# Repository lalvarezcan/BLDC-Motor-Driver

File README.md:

# BLDC Motor Driver for MIT Mini Cheetah Actuator

This driver is designed specifically for use with the Quasi-Direct Driver (QDD) Actuators, inspired by the work of Ben Katz. The driver is intended to efficiently deliver power and control a BLDC Motor, enabling precise and agile movements.

## Overview

The BLDC Motor Driver is a crucial component in the Quasi-Driect Drive (QDD) Actuator system, responsible for managing the power and control signals sent to the brushless DC motors. It ensures smooth operation, speed control, and torque management for the actuators, contributing to the overall performance of the robotic system.

## Features

- **Brushless DC Motor Control:** Offers precise control over the motors used in the Mini Cheetah Actuator.
- **PWM (Pulse Width Modulation) Control:** Enables accurate speed control and torque management.
- **Communication Interface:** Interfaces with the main control system via a specified communication protocol (e.g., SPI, CAN, UART).
- **Overcurrent and Overvoltage Protection:** Safeguards the system and motors against potential damage due to excessive current or voltage.

## Hardware Requirements

- **BLDC Motors:** Compatible with the motors specified for the MIT Mini Cheetah Actuator.
- **Microcontroller or Control Board:** Interfaces with the driver to send control signals.
- **Power Supply:** Provides the necessary voltage and current for the motors.

## Installation and Setup

1. **Hardware Connections:** Connect the driver to the specified ports on the control board and motors as per the provided documentation or pinout details.
2. **Power Supply:** Ensure the power supply meets the voltage and current requirements of the motors.
3. **Control Interface:** Establish communication between the driver and the main control system using the designated communication protocol.
4. **Software Integration:** Implement the necessary control algorithms or software libraries to interact with the driver and control the motors effectively.

## Usage

- **Initialization:** Initialize the driver and configure the necessary parameters (e.g., PWM frequency, motor direction, etc.).
- **Control Commands:** Send control commands via the designated communication interface to adjust motor speed, direction, and torque as required.
- **Monitoring:** Implement monitoring mechanisms to keep track of motor performance, temperature, and any potential faults.

## Contributors

- Luis Avarez (CINVESTAV Guadalajara)

## License

This project is licensed under [MIT License](LICENSE.md).

## Acknowledgments

- Ben Katz (Original MIT Mini Cheetah Actuator Design)

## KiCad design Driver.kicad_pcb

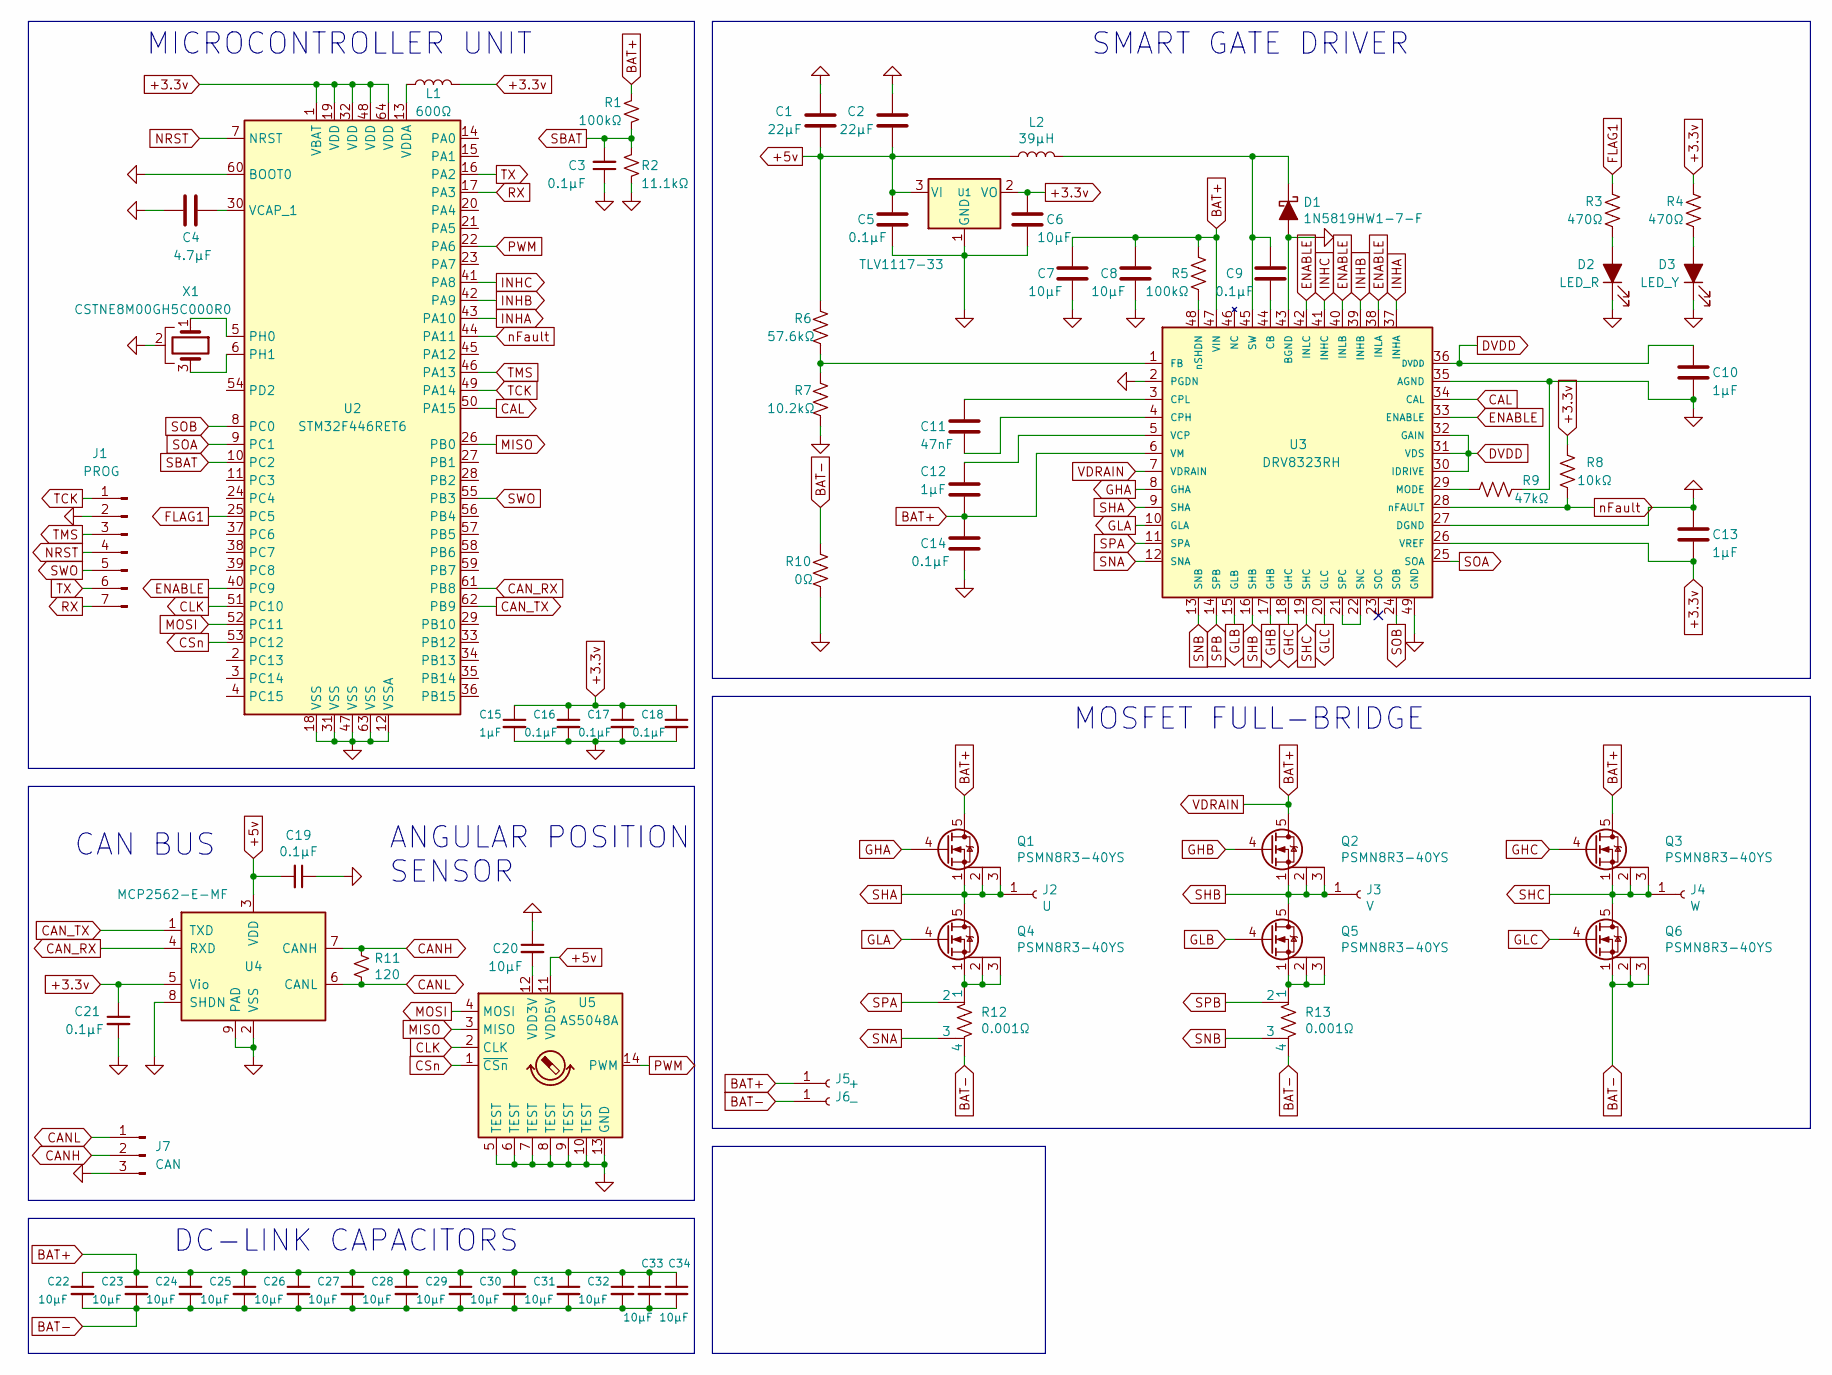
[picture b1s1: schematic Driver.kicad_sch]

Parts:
C1, C2: 22µF; C_0805_2012Metric
C3, C5, C9, C14, C16, C17, C18, C19, C21: 0.1µF; C_0805_2012Metric
C4: 4.7µF; C_0805_2012Metric
C6, C7, C8, C20: 10µF; C_0805_2012Metric
C10, C12, C13, C15: 1µF; C_0805_2012Metric
C11: 47nF; C_0805_2012Metric
C22, C23, C24, C25, C26, C27, C28, C29, C30, C31, C32, C33, C34: 10µF; C_1206_3216Metric
D1: 1N5819HW1-7-F; D_SOD-123F
D2: LED_R; LED_0603_1608Metric_Pad1.05x0.95mm_HandSolder
D3: LED_Y; LED_0603_1608Metric_Pad1.05x0.95mm_HandSolder
J1: PROG; JST_SH_SM07B-SRSS-TB_1x07-1MP_P1.00mm_Horizontal
J2: U; drillhole
J3: V; drillhole
J4: W; drillhole
J5: +; drillhole
J6: -; drillhole
J7: CAN; JST_SH_SM03B-SRSS-TB_1x03-1MP_P1.00mm_Horizontal
L1: 600Ω; L_0805_2012Metric
L2: 39µH; ELL6UH390M
Q1, Q2, Q3, Q4, Q5, Q6: PSMN8R3-40YS; LFPAK56
R1, R5: 100kΩ; R_0805_2012Metric
R2: 11.1kΩ; R_0805_2012Metric
R3, R4: 470Ω; R_0805_2012Metric
R6: 57.6kΩ; R_0805_2012Metric
R7: 10.2kΩ; R_0805_2012Metric
R8: 10kΩ; R_0805_2012Metric
R9: 47kΩ; R_0805_2012Metric
R10: 0Ω; R_1206_3216Metric
R11: 120; R_0805_2012Metric
R12, R13: 0.001Ω; R_Shunt_2512_6332Metric
U1: TLV1117-33; Texas_S-PVSON-N8
U2: STM32F446RET6; LQFP-64_10x10mm_P0.5mm
U3: DRV8323RH; Texas_S-PVQFN-N48_EP5.15x5.15mm_ThermalVias
U4: MCP2562-E-MF; DFN-8-1EP_3x3mm_P0.65mm_EP1.55x2.4mm
U5: AS5048A; TSSOP-14_4.4x5mm_P0.65mm
X1: CSTNE8M00GH5C000R0; Resonator_SMD_muRata_CSTxExxV-3Pin_3.0x1.1mm

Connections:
+3.3v: C6.2, C13.1, C15.1, C16.1, C17.1, C18.1, C21.1, L1.2, R4.2, R8.1, U1.2 (VO), U2.1 (VBAT), U2.19 (VDD), U2.32 (VDD), U2.48 (VDD), U2.64 (VDD), U3.26 (VREF), U4.5 (Vio)
+5v: C1.2, C2.2, C5.2, C19.2, L2.1, R6.1, U1.3 (VI), U4.3 (VDD), U5.11 (VDD5V)
BAT+: C7.2, C8.2, C12.1, C14.2, C22.1, C23.1, C24.1, C25.1, C26.1, C27.1, C28.1, C29.1, C30.1, C31.1, C32.1, C33.1, C34.1, J5.1, Q1.5 (D), Q2.5 (D), Q3.5 (D), R1.1, R5.2, U3.6 (VM), U3.7 (VDRAIN), U3.47 (VIN)
BAT-: C22.2, C23.2, C24.2, C25.2, C26.2, C27.2, C28.2, C29.2, C30.2, C31.2, C32.2, C33.2, C34.2, J6.1, Q6.1 (S), Q6.2 (S), Q6.3 (S), R10.1, R12.4, R13.4
CAL: U2.50 (PA15), U3.34 (CAL)
CANH: J7.2, R11.1, U4.7 (CANH)
CANL: J7.1, R11.2, U4.6 (CANL)
CAN_RX: U2.61 (PB8), U4.4 (RXD)
CAN_TX: U2.62 (PB9), U4.1 (TXD)
CLK: U2.51 (PC10), U5.2 (CLK)
CSn: U2.53 (PC12), U5.1 (~CSn)
DVDD: C10.2, U3.30 (IDRIVE), U3.31 (VDS), U3.32 (GAIN), U3.36 (DVDD)
ENABLE: U2.40 (PC9), U3.33 (ENABLE), U3.38 (INLA), U3.40 (INLB), U3.42 (INLC)
FLAG1: R3.2, U2.25 (PC5)
GHA: Q1.4 (G), U3.8 (GHA)
GHB: Q2.4 (G), U3.17 (GHB)
GHC: Q3.4 (G), U3.18 (GHC)
GLA: Q4.4 (G), U3.10 (GLA)
GLB: Q5.4 (G), U3.15 (GLB)
GLC: Q6.4 (G), U3.20 (GLC)
GND: C1.1, C2.1, C3.1, C4.1, C5.1, C6.1, C7.1, C8.1, C10.1, C13.2, C14.1, C15.2, C16.2, C17.2, C18.2, C19.1, C20.1, C21.2, D1.2 (A), D2.1 (K), D3.1 (K), J1.2, J7.3, R2.1, R7.2, R9.2, R10.2, U1.1 (GND), U2.12 (VSSA), U2.18 (VSS), U2.31 (VSS), U2.47 (VSS), U2.60 (BOOT0), U2.63 (VSS), U3.2 (PGDN), U3.27 (DGND), U3.35 (AGND), U3.43 (BGND), U3.49 (GND), U4.2 (VSS), U4.8 (SHDN), U4.9 (PAD), U5.5 (TEST), U5.6 (TEST), U5.7 (TEST), U5.8 (TEST), U5.9 (TEST), U5.10 (TEST), U5.13 (GND), X1.2
INHA: U2.43 (PA10), U3.37 (INHA)
INHB: U2.42 (PA9), U3.39 (INHB)
INHC: U2.41 (PA8), U3.41 (INHC)
MISO: U2.26 (PB0), U5.3 (MISO)
MOSI: U2.52 (PC11), U5.4 (MOSI)
NRST: J1.4, U2.7 (NRST)
unnamed: C4.2, U2.30 (VCAP_1)
unnamed: C9.1, U3.44 (CB)
unnamed: C9.2, D1.1 (K), L2.2, U3.45 (SW)
unnamed: C11.1, U3.4 (CPH)
unnamed: C11.2, U3.3 (CPL)
unnamed: C12.2, U3.5 (VCP)
unnamed: C20.2, U5.12 (VDD3V)
unnamed: D2.2 (A), R3.1
unnamed: D3.2 (A), R4.1
unnamed: L1.1, U2.13 (VDDA)
unnamed: Q4.1 (S), Q4.2 (S), Q4.3 (S), R12.1
unnamed: Q5.1 (S), Q5.2 (S), Q5.3 (S), R13.1
unnamed: R5.1, U3.48 (nSHDN)
unnamed: R6.2, R7.1, U3.1 (FB)
unnamed: R9.1, U3.29 (MODE)
unnamed: U2.5 (PH0), X1.1
unnamed: U2.6 (PH1), X1.3
unnamed: U3.21 (SPC), U3.22 (SNC)
PWM: U2.22 (PA6), U5.14 (PWM)
RX: J1.7, U2.17 (PA3)
SBAT: C3.2, R1.2, R2.2, U2.10 (PC2)
SHA: J2.1, Q1.1 (S), Q1.2 (S), Q1.3 (S), Q4.5 (D), U3.9 (SHA)
SHB: J3.1, Q2.1 (S), Q2.2 (S), Q2.3 (S), Q5.5 (D), U3.16 (SHB)
SHC: J4.1, Q3.1 (S), Q3.2 (S), Q3.3 (S), Q6.5 (D), U3.19 (SHC)
SNA: R12.3, U3.12 (SNA)
SNB: R13.3, U3.13 (SNB)
SOA: U2.9 (PC1), U3.25 (SOA)
SOB: U2.8 (PC0), U3.24 (SOB)
SPA: R12.2, U3.11 (SPA)
SPB: R13.2, U3.14 (SPB)
SWO: J1.5, U2.55 (PB3)
TCK: J1.1, U2.49 (PA14)
TMS: J1.3, U2.46 (PA13)
TX: J1.6, U2.16 (PA2)
nFault: R8.2, U2.44 (PA11), U3.28 (nFAULT)

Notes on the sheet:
MOSFET FULL-BRIDGE
CAN BUS
ANGULAR POSITION SENSOR
SMART GATE DRIVER
DC-LINK CAPACITORS
MICROCONTROLLER UNIT

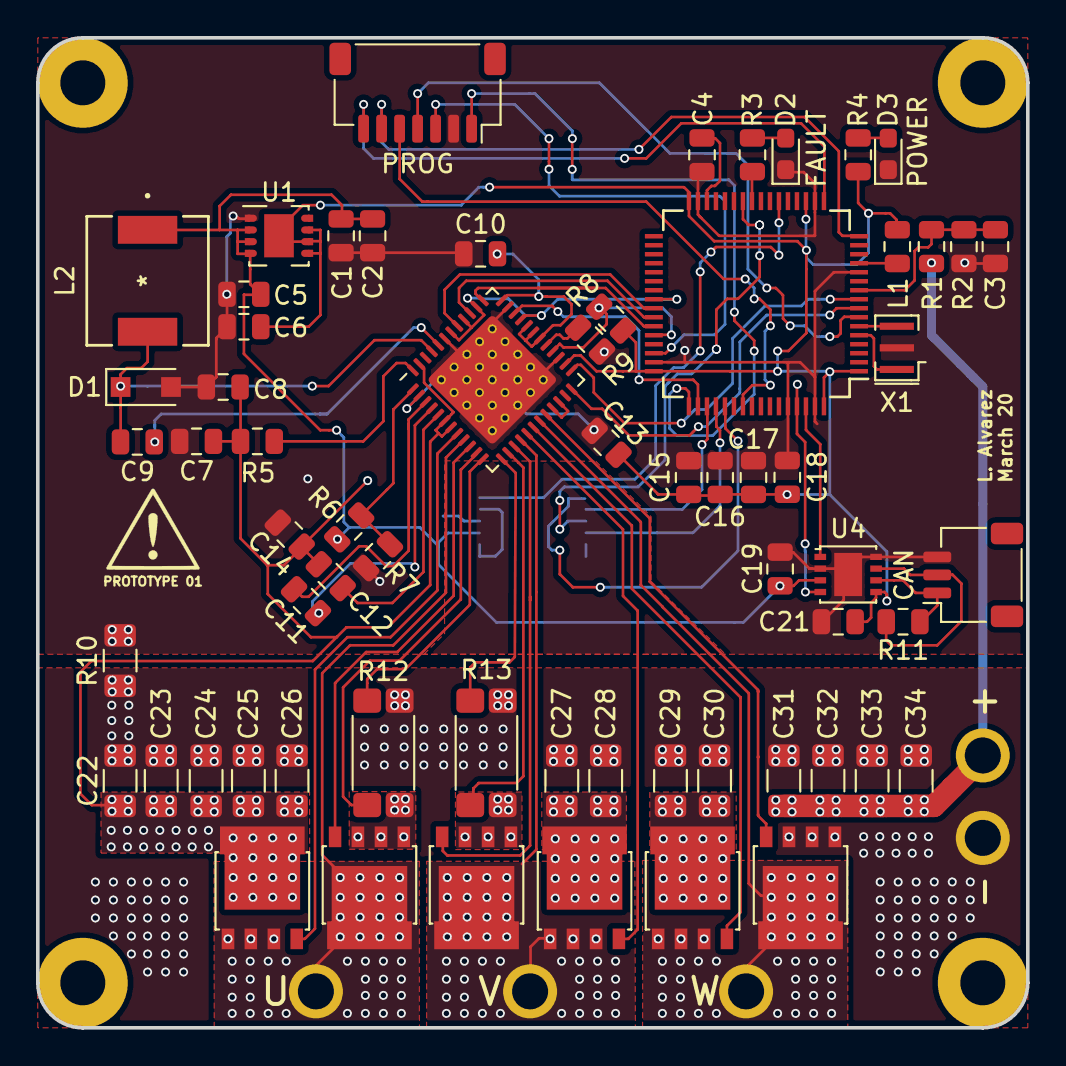
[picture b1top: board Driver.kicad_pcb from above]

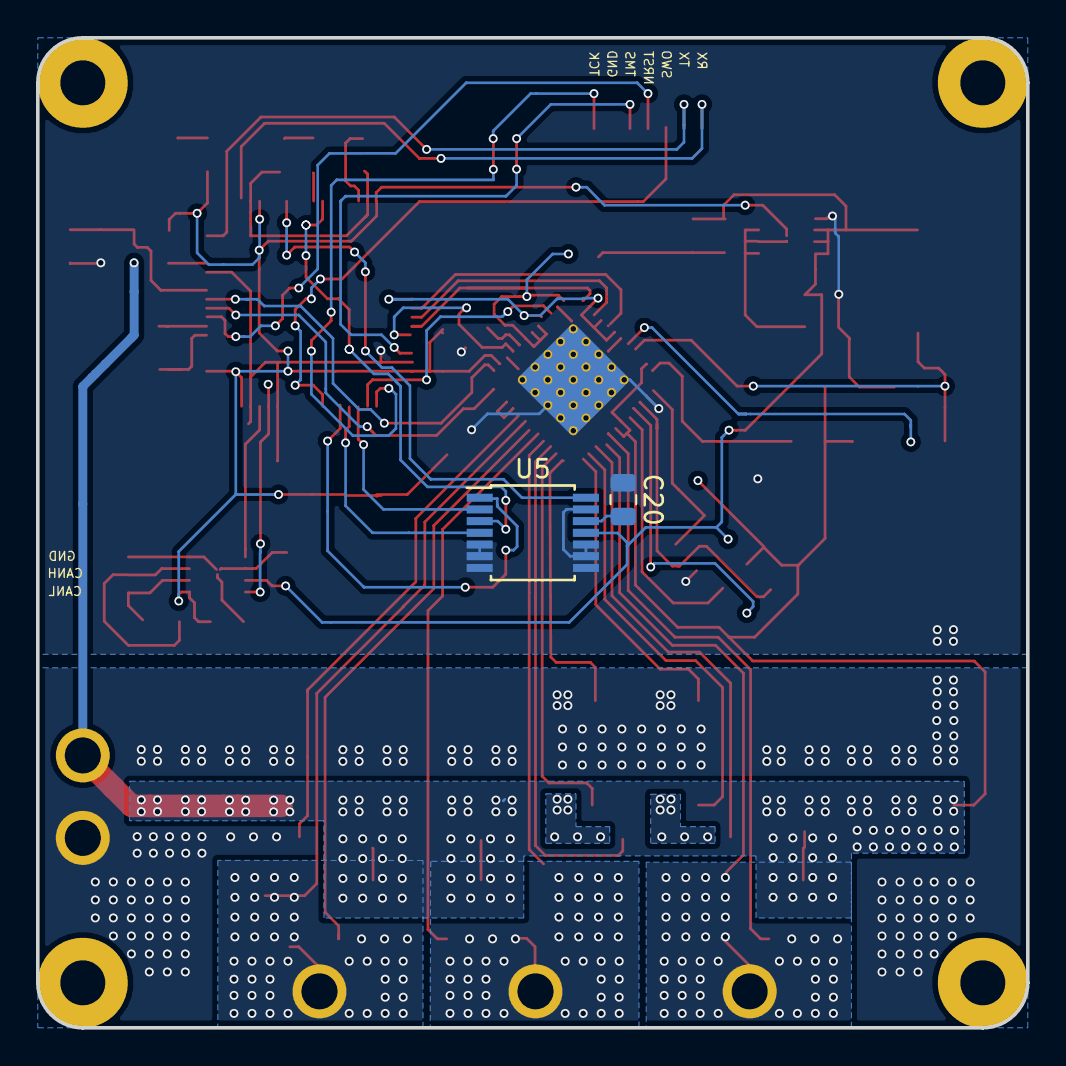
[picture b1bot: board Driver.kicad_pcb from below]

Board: 2 copper layers, 55.0 x 55.0 mm, 71 parts (2 on the bottom side), 62 nets.
